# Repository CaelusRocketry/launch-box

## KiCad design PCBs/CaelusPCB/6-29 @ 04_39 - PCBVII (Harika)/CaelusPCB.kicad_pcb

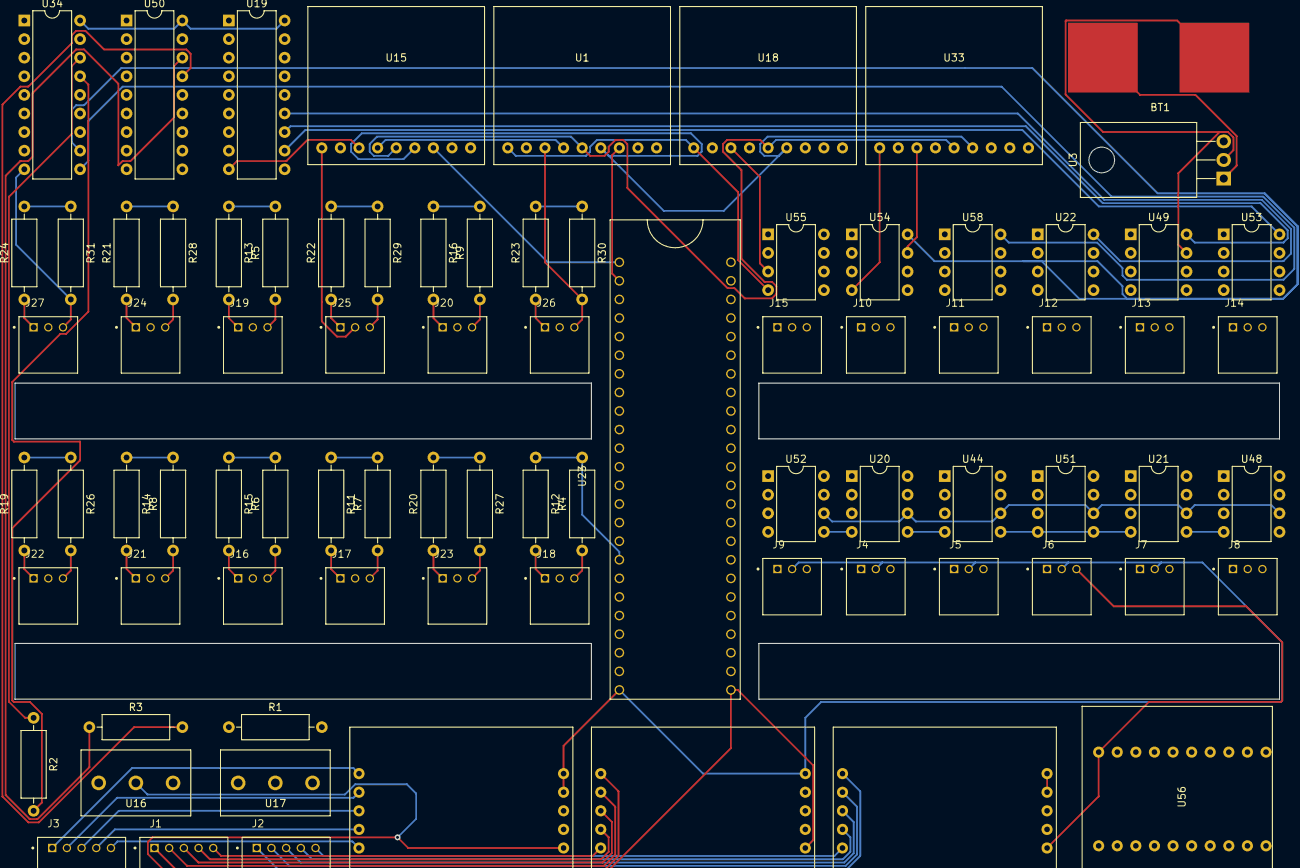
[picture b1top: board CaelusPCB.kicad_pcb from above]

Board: 2 copper layers, 82 parts (0 on the bottom side), 104 nets.

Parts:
BT1: Battery_Cell; Lipo_Battery_Connector
J1, J2, J3: 440055-5; 5_Header
J4, J5, J6, J7, J8, J9, J10, J11, J12, J13, J14, J15, J16, J17, J18, J19, J20, J21, J22, J23, J24, J25, J26, J27: 440055-3; 3_Header
R1, R2, R3, R4, R5, R6, R7, R8, R9, R11, R12, R13, R14, R15, R16, R19, R20, R21, R22, R23, R24, R26, R27, R28, R29, R30, R31: R_US; R_Axial_DIN0309_L9.0mm_D3.2mm_P12.70mm_Horizontal
U1, U15, U18, U33: MAX31856
U3: L7805; TO-220-3_Horizontal_TabDown
U16, U17: SerialScrewTerminals; ScrewTerminals
U19, U34, U50: Launchbox_HT12D; DIP-18_W7.62mm
U20, U21, U22, U44, U48, U49, U51, U52, U53, U54, U55, U58: SPDT_IC; DIP-8_W7.62mm
U23: Teensy3.6; Teensy 3.6
U25, U36, U46: LoadCellAmp
U56: XBee_Breakout; Xbee_Breakout

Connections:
1: U1.4, U15.4, U18.4, U23.32, U33.4
2: U23.31, U33.7
3: U20.2, U23.3
3.3: U23.47, U56.1
4: U23.4, U44.2
5: U23.5, U51.2
6: U21.2, U23.6
7: U23.39, U48.2
8: U23.13, U52.2
9: U23.9, U54.2
10: U23.10, U58.2
11: U22.2, U23.11
12: U23.12, U49.2
13: U1.6, U15.6, U18.6, U23.0, U33.6
14: U1.5, U15.5, U18.5, U23.1, U33.5
15: U18.7, U23.2
16: U23.25, U25.8
17: U23.26, U25.7
18: U23.27, U36.8
19: U23.28, U36.7
20: U23.29, U46.8
21: U23.30, U46.7
25: U17.1, U50.14
26: U17.2, U34.14
27: U17.3, U19.14
28: U20.8, U50.13
29: U44.8, U50.12
30: U50.11, U51.8
31: U21.8, U50.10
32: U34.13, U48.8
33: U34.12, U52.8
34: U34.11, U54.8
35: U34.10, U58.8
36: U19.13, U22.8
37: U19.12, U49.8
38: U19.11, U53.8
39: U19.10, U55.8
40: J4.1, U20.1
41: J5.1, U44.1
42: J6.1, U51.1
43: J7.1, U21.1
44: J8.1, U48.1
45: J9.1, U52.1
46: J10.1, U54.1
47: J11.1, U58.1
48: J12.1, U22.1
49: J13.1, U49.1
50: U15.7, U23.33
51: U1.7, U23.34
52: U16.1, U20.6, U21.6, U22.6, U44.6, U48.6, U49.6, U51.6, U52.6, U53.6, U54.6, U55.6, U58.6
53: J14.1, U53.1
54: J15.1, U55.1
57: U23.24, U53.2
58: U23.35, U55.2
60: U23.8, U56.3
61: U23.7, U56.2
+5V: J4.2, J5.2, J6.2, J7.2, J8.2, J9.2, J10.2, J11.2, J12.2, J13.2, J14.2, J15.2, J16.2, J17.2, J18.2, J19.2, J20.2, J21.2, J22.2, J23.2, J24.2, J25.2, J26.2, J27.2, U1.1, U3.3, U15.1, U18.1, U19.18, U20.4, U20.5, U21.4, U21.5, U22.4, U22.5, U23.40, U25.9, U25.10, U33.1, U34.18, U36.9, U36.10, U44.4, U44.5, U46.9, U46.10, U48.4, U48.5, U49.4, U49.5, U50.18, U51.4, U51.5, U52.4, U52.5, U53.4, U53.5, U54.4, U54.5, U55.4, U55.5, U58.4, U58.5
GND1: BT1.2, J4.3, J5.3, J6.3, J7.3, J8.3, J9.3, J10.3, J11.3, J12.3, J13.3, J14.3, J15.3, J16.3, J17.3, J18.3, J19.3, J20.3, J21.3, J22.3, J23.3, J24.3, J25.3, J26.3, J27.3, R4.1, R5.1, R6.1, R7.1, R8.1, R9.1, R26.2, R27.2, R28.2, R29.2, R30.2, R31.2, U1.3, U3.2, U15.3, U16.2, U18.3, U19.9, U20.3, U20.7, U21.3, U21.7, U22.3, U22.7, U23.46, U25.6, U33.3, U34.9, U36.6, U44.3, U44.7, U46.6, U48.3, U48.7, U49.3, U49.7, U50.9, U51.3, U51.7, U52.3, U52.7, U53.3, U53.7, U54.3, U54.7, U55.3, U55.7, U56.10, U58.3, U58.7
unnamed: BT1.1, U3.1
unnamed: J1.1, U25.1
unnamed: J1.2, U25.2
unnamed: J1.3, U25.3
unnamed: J1.4, U25.4
unnamed: J1.5, U25.5
unnamed: J2.1, U36.1
unnamed: J2.2, U36.2
unnamed: J2.3, U36.3
unnamed: J2.4, U36.4
unnamed: J2.5, U36.5
unnamed: J3.1, U46.1
unnamed: J3.2, U46.2
unnamed: J3.3, U46.3
unnamed: J3.4, U46.4
unnamed: J3.5, U46.5
unnamed: J16.1, R15.2
unnamed: J17.1, R11.2
unnamed: J18.1, R12.2
unnamed: J19.1, R13.2
unnamed: J20.1, R16.2
unnamed: J21.1, R14.2
unnamed: J22.1, R19.1
unnamed: J23.1, R20.1
unnamed: J24.1, R21.1
unnamed: J25.1, R22.1
unnamed: J26.1, R23.1
unnamed: J27.1, R24.1
unnamed: R1.1, U19.16
unnamed: R1.2, U19.15
unnamed: R2.1, U34.16
unnamed: R2.2, U34.15
unnamed: R3.1, U50.16
unnamed: R3.2, U50.15
unnamed: R7.2, R11.1, U23.21
unnamed: R4.2, R12.1, U23.19
unnamed: R5.2, R13.1, U23.17
unnamed: R8.2, R14.1, U23.38
unnamed: R6.2, R15.1, U23.23
unnamed: R9.2, R16.1, U23.15
unnamed: R19.2, R26.1, U23.22
unnamed: R20.2, R27.1, U23.20
unnamed: R21.2, R28.1, U23.18
unnamed: R22.2, R29.1, U23.16
unnamed: R23.2, R30.1, U23.14
unnamed: R24.2, R31.1, U23.37

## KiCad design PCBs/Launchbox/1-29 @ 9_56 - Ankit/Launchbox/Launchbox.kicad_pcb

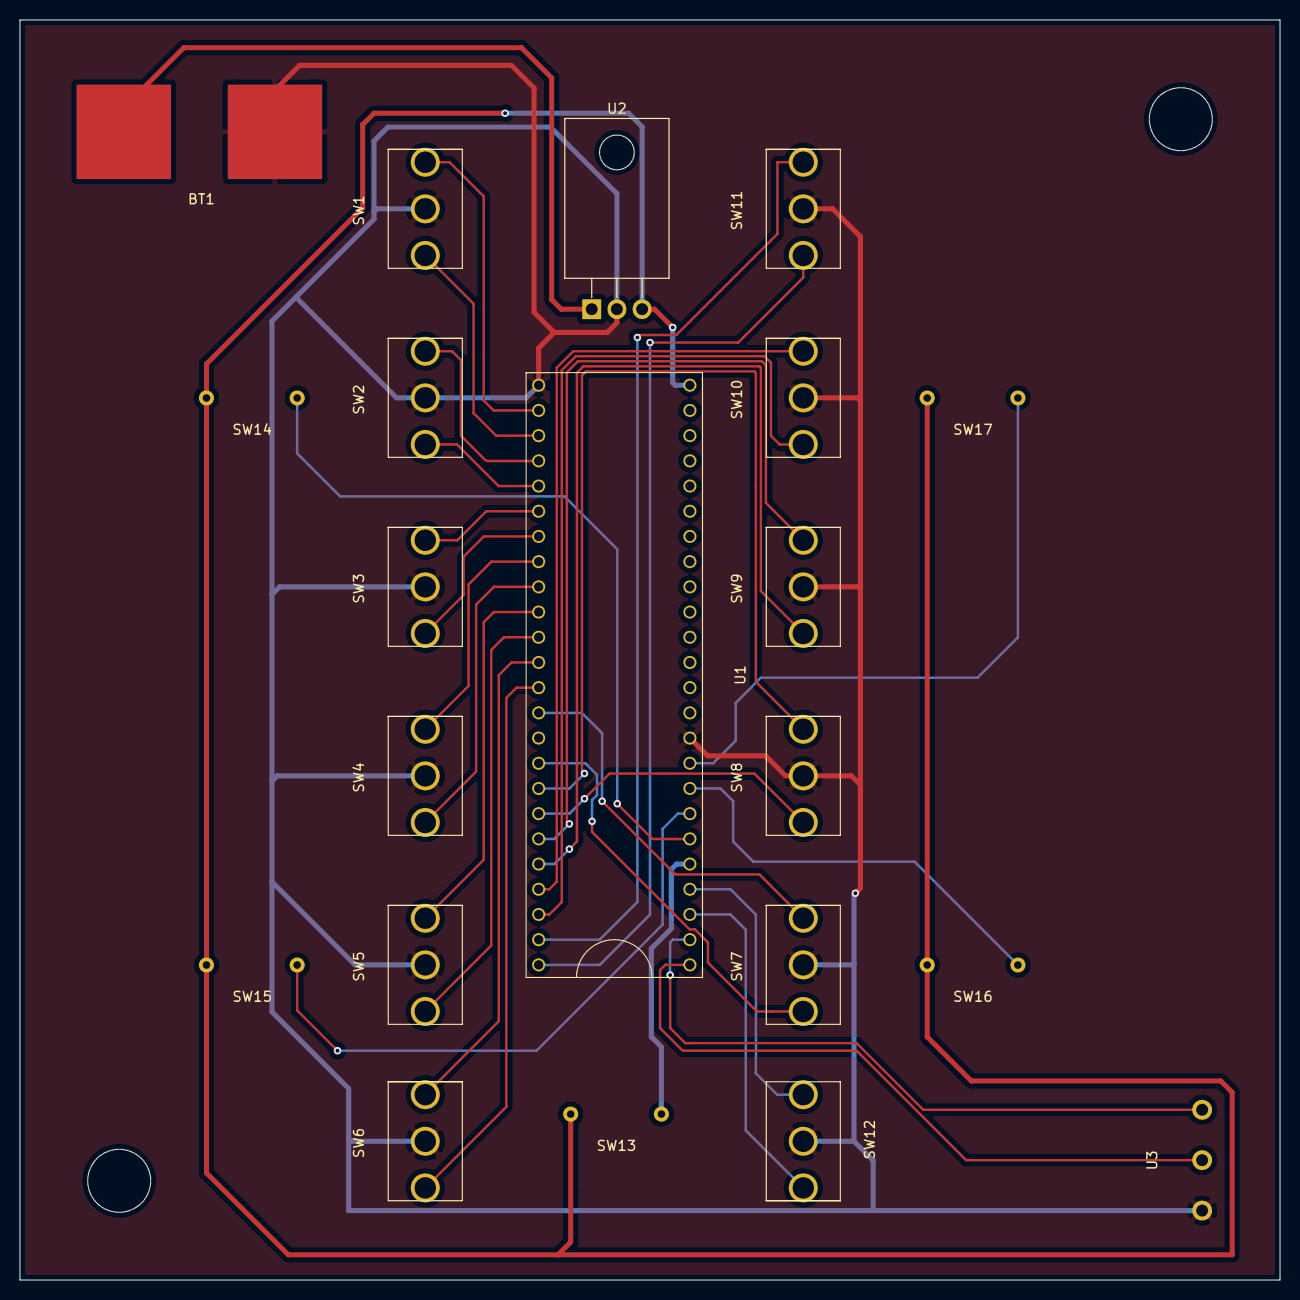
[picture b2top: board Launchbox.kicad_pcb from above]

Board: 2 copper layers, 127.0 x 127.0 mm, 21 parts (0 on the bottom side), 34 nets.

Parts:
BT1: Battery_Cell; Lipo_Battery_Connector
SW1, SW2, SW3, SW4, SW5, SW6, SW7, SW8, SW9, SW10, SW11, SW12: SW_SPDT_MSM; SPDT_Slide_Switch
SW13, SW14, SW15, SW16, SW17: SW_Push; Pushbutton
U1: Teensy3.6; Teensy 3.6
U2: L7805; TO-220F-3_Horizontal_TabDown
U3: SerialScrewTerminals; ScrewTerminals

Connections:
GND: BT1.2, SW1.2, SW2.2, SW3.2, SW4.2, SW5.2, SW6.2, SW7.2, SW8.2, SW9.2, SW10.2, SW11.2, SW12.2, U1.43, U1.46, U2.2, U3.3
unnamed: BT1.1, U2.1
unnamed: SW1.1, U1.0
unnamed: SW1.3, U1.1
unnamed: SW2.1, U1.2
unnamed: SW2.3, U1.3
unnamed: SW3.1, U1.4
unnamed: SW3.3, U1.5
unnamed: SW4.1, U1.6
unnamed: SW4.3, U1.7
unnamed: SW5.1, U1.8
unnamed: SW5.3, U1.9
unnamed: SW6.1, U1.10
unnamed: SW6.3, U1.11
unnamed: SW7.1, U1.12
unnamed: SW7.3, U1.24
unnamed: SW8.1, U1.25
unnamed: SW8.3, U1.26
unnamed: SW9.1, U1.27
unnamed: SW9.3, U1.28
unnamed: SW10.1, U1.29
unnamed: SW10.3, U1.30
unnamed: SW11.1, U1.31
unnamed: SW11.3, U1.32
unnamed: SW12.1, U1.35
unnamed: SW12.3, U1.36
unnamed: SW13.1, SW14.1, SW15.1, SW16.1, SW17.1, U1.40, U2.3
unnamed: SW13.2, U1.37
unnamed: SW14.2, U1.38
unnamed: SW15.2, U1.39
unnamed: SW16.2, U1.45
unnamed: SW17.2, U1.44
unnamed: U1.33, U3.2
unnamed: U1.34, U3.1
